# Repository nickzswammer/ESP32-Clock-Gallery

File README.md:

# ESP32 E-Paper Clock / Gallery Display

  |  | 
  |:--:| 
  | *Clock Frontside* |

A customizable ESP32-based image clock gallery project, combining Arduino firmware, Python scripting, electronics, and PCB design. This project allows users to upload images via a web interface, convert them to a binary format suitable for display on a clock-style device, and manage them on the ESP32.

---

## Features

  |  | 
  |:--:| 
  | *Power Management Block Diagram* |

- **Embedded / Microcontroller:**
  - ESP32 main controller
  - Real-Time Clock (RTC) module for accurate timekeeping
  - Pushbutton controls for menu and navigation
  - SPI and I²C interfaces for peripheral communication

- **Python Backend:**
  - Flask web server for uploading images
  - Automated image conversion to `.bin` format with dithering
  - Image resizing and centering for consistent display
  - Batch download as ZIP archives for easy transfer to the ESP32

- **Electronics & PCB:**
  - 2-layer custom PCB design
  - Integrated power circuitry with MOSFET-based power muxing
  - Battery protection and charging circuitry
  - SPI and I²C routed to peripherals for modularity

  |  | 
  |:--:| 
  | *Internal Component View* |

---

## Image Processing Workflow

1. Users upload images via the Flask web interface.
2. Images are resized to fit a **400×300 display resolution**, converted to grayscale, and dithered to 1-bit black and white.
3. The processed images are converted into a `.bin` file containing:
   - 2-byte width
   - 2-byte height
   - Pixel data in row-major order
4. All processed `.bin` files can be downloaded in a ZIP archive for easy transfer to the ESP32.

---

## Folder Structure

```

project_root/
├── image_processor/      # Python backend
│   ├── uploaded_files/       # Raw uploaded images
│   ├── processed_files/      # Converted .bin images
│   ├── zipped_files/         # Zip archives of processed images
│   ├── templates/            # Flask HTML templates
│   ├── index.html
│   ├── static/               # Optional CSS/JS for Flask
│   ├── app.py                # Flask backend and image processing
│   └── download_zip.html
├── GxEPD2_display_selection_new_style.h # GxEPD2 Library E-Paper Display Select
├── GxEPD2_selection_check.h             
├── WebHelpers.cpp                       # Helper functions for the upload/ webserver processing
├── WebHelpers.h         
├── full_disp_AND_upload.ino             # Full Arduino file containing firmware for clock functionality
└── README.md 

````
---

## ESP32 Hardware and Firmware

### Hardware

* **ESP32 Microcontroller**: Handles display updates, button input, RTC communication, and Wi-Fi connectivity.
* **GxEPD2 E-Ink Display**: SPI-connected, supports partial/full updates for low power.
* **MicroSD Card**: Stores images for display; accessed via SPI.
* **DS3231 RTC**: Provides accurate time over I²C.
* **MAX17043 Fuel Gauge**: Monitors LiPo battery percentage.
* **Buttons**: Four GPIO-connected buttons for menu navigation and mode switching.
* **Power Management**: Supports light/deep sleep; wake on button or timer.

### Firmware

* **Initialization**: Sets up peripherals, Wi-Fi, and web server.
* **Main Loop**: Handles button input, updates clock display, manages sleep, and serves web requests.
* **Gallery Management**: Reads images from SD card, navigates files, and supports slideshow.
* **Power Optimization**: Disables unused peripherals and enters sleep during inactivity.

---

## PCB & Electronics

|  | 
|:--:| 
| *PCB Layout View* |

- **2-layer PCB:**
  - Integrated power supply with custom MOSFET power muxing
  - Battery protection and charging
  - SPI and I²C routing for peripheral modules
  - ESP32 microcontroller footprint with all required signals exposed

- **Peripherals:**
  - RTC module
  - Pushbuttons for user input
  - Optional displays (LCD, OLED, or e-paper)

- **Circuit Features:**
  - Power management: allows USB and battery operation
  - Safe charging and overcurrent protection
  - Modular design for easy hardware expansion

---

## Case & Mechanical Design

- Custom enclosure design in Fusion 360 to fit the ESP32 PCB and display
- Mounting points for pushbuttons
- Openings for charging port, buttons, and display window
- 3d printed

---

## Author

**Nicholas Zhang**

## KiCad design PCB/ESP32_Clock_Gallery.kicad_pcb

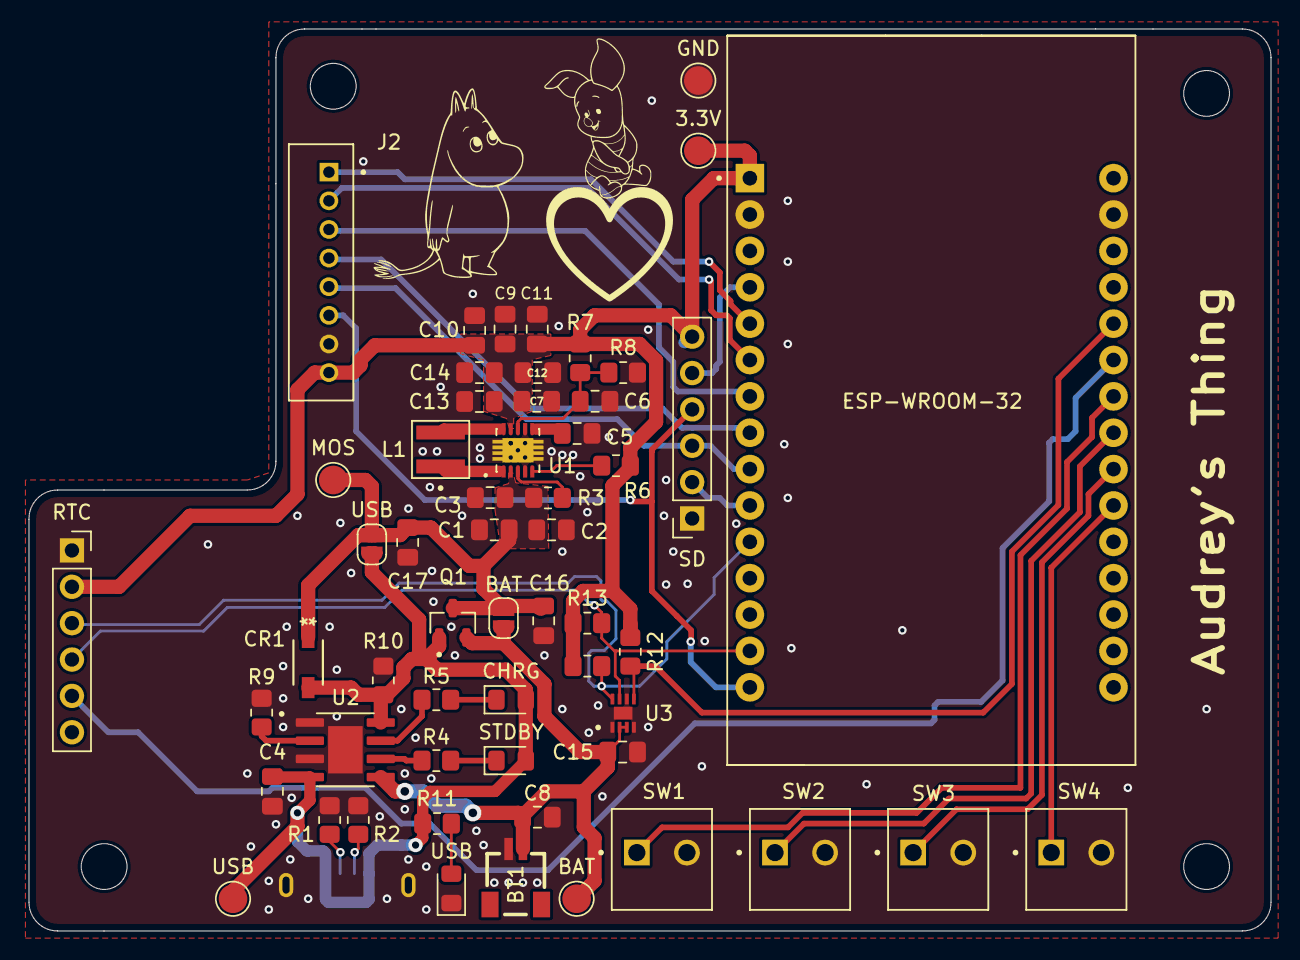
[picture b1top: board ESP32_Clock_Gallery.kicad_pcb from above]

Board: 2 copper layers, 86.8 x 63.0 mm, 57 parts (1 on the bottom side), 35 nets.

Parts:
3.3V: TestPoint; TestPoint_Pad_D2.0mm
BAT: SolderJumper_2_Open; SolderJumper-2_P1.3mm_Open_RoundedPad1.0x1.5mm
BAT#2: TestPoint; TestPoint_Pad_D2.0mm
BT1: 3.7V 1500mAh LiPo; SM02B-SRSS-TB_LF__SN_
C1, C2, C4, C8, C9, C10, C11, C12, C13, C14, C16, C17: 10uF; C_0805_2012Metric_Pad1.18x1.45mm_HandSolder
C3, C5, C7, C15: 0.1uF; C_0805_2012Metric_Pad1.18x1.45mm_HandSolder
C6: 2.2pF; C_0805_2012Metric_Pad1.18x1.45mm_HandSolder
CHRG: LED; LED_0805_2012Metric_Pad1.15x1.40mm_HandSolder
CR1: B5819W-TP; SDO_SOD-123_MCC-M
ESP-WROOM-32: ESP-WROOM-32 Dev Module; MODULE_ESP32_DEVKIT_V1
GND: TestPoint; TestPoint_Pad_D2.0mm
J1: UJC-V-G-SMT-P6-TR; SAMESKY_UJC-V-G-SMT-P6-TR
J2: B8B-PH-K-S_LF__SN_; JST_B8B-PH-K-S_LF__SN_
L1: 1.2 uH; IND_XFL4020-102MEC
MOS: TestPoint; TestPoint_Pad_D2.0mm
Q1: PMOS; SOT95P237X112-3N
R1, R2: 5.1K; R_0805_2012Metric_Pad1.20x1.40mm_HandSolder
R3, R6: 100K; R_0805_2012Metric_Pad1.20x1.40mm_HandSolder
R4, R5: 1K; R_0805_2012Metric_Pad1.20x1.40mm_HandSolder
R7: 360K; R_0805_2012Metric_Pad1.20x1.40mm_HandSolder
R8: 64.9K; R_0805_2012Metric_Pad1.20x1.40mm_HandSolder
R9: 1.5K; R_0805_2012Metric_Pad1.20x1.40mm_HandSolder
R10, R12: 10K; R_0805_2012Metric_Pad1.20x1.40mm_HandSolder
R11: 470; R_0805_2012Metric_Pad1.20x1.40mm_HandSolder
R13, R14: 4.7K; R_0805_2012Metric_Pad1.20x1.40mm_HandSolder
RTC: DS3231 Breakout; PinSocket_1x06_P2.54mm_Vertical
SD: MicroSD Breakout; PinSocket_1x06_P2.54mm_Vertical
STDBY: LED; LED_0805_2012Metric_Pad1.15x1.40mm_HandSolder
SW1, SW2, SW3, SW4: DB301V-3.5-2P-GN-S; PHOENIX_1984617
U1: TPS63060; CONV_TPS63060DSCT
U2: TP4056; SOP127P600X175-9N
U3: MAX17048G_T10; SON50P200X200X80-9N
USB: SolderJumper_2_Open; SolderJumper-2_P1.3mm_Open_RoundedPad1.0x1.5mm
USB#2: TestPoint; TestPoint_Pad_D2.0mm
USB#3: LED; LED_0805_2012Metric_Pad1.15x1.40mm_HandSolder

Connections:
+3V3: 3.3V.1, C7.1, C9.1, C10.1, C11.1, C12.1, C13.1, C14.1, ESP-WROOM-32.1 (3V3), J2.8, R6.1, R7.1, R12.1, R13.1, R14.1, RTC.2 (VCC), SD.6 (3V3), U1.9 (VOUT)
/ESP32/ALRT: ESP-WROOM-32.26 (D14), R12.2, U3.5 (~ALERT)
/ESP32/B1: ESP-WROOM-32.24 (D26), SW1.1
/ESP32/B2: ESP-WROOM-32.23 (D25), SW2.1
/ESP32/B3: ESP-WROOM-32.22 (D33), SW3.1
/ESP32/B4: ESP-WROOM-32.21 (D32), SW4.1
/ESP32/BUSY: ESP-WROOM-32.5 (D4), J2.1
/ESP32/CLK: ESP-WROOM-32.9 (D18), J2.5, SD.3 (CLK)
/ESP32/CS_DISP: ESP-WROOM-32.8 (D5), J2.4
/ESP32/CS_SD: ESP-WROOM-32.4 (D2), SD.5 (CS)
/ESP32/DC: ESP-WROOM-32.7 (TX2(17)), J2.3
/ESP32/MISO: ESP-WROOM-32.10 (D19), SD.2 (MISO)
/ESP32/MOSI: ESP-WROOM-32.15 (D23), J2.6, SD.4 (MOSI)
/ESP32/RST: ESP-WROOM-32.6 (RX2(16)), J2.2
/ESP32/SCL: ESP-WROOM-32.14 (D22), R13.2, RTC.4 (SCL), U3.7 (SCL)
/ESP32/SDA: ESP-WROOM-32.11 (D21), R14.2, RTC.3 (SDA), U3.8 (SDA)
/ESP32/SQW: ESP-WROOM-32.25 (D27), RTC.5 (SQW)
/Power/3.7V_BAT: BAT.1 (A), BAT#2.1, BT1.2 (-), C8.1, C15.1, Q1.2, U2.5 (BAT), U3.2 (CELL), U3.3 (VDD)
/Power/5V_USB: C4.1, CHRG.2 (A), CR1.2, J1.A9 (VBUS), J1.B9 (VBUS__1), Q1.1, R10.1, R11.2, STDBY.2 (A), U2.4 (VCC), U2.8 (CE), USB.1 (A), USB#2.1
/Power/MOS_OUT: BAT.2 (B), C1.1, C2.1, C3.1, C16.1, C17.1, CR1.1, MOS.1, Q1.3, R3.1, U1.2 (VIN), USB.2 (B)
GND: BT1.1 (+), C1.2, C2.2, C3.2, C4.2, C5.2, C6.2, C7.2, C8.2, C9.2, C10.2, C11.2, C12.2, C13.2, C14.2, C15.2, C16.2, C17.2, ESP-WROOM-32.2 (GND), ESP-WROOM-32.29 (GND), GND.1, J1.A12 (GND), J1.B12 (GND__1), J1.SH1 (SHIELD), J1.SH2 (SHIELD__1), J2.7, R1.1, R2.1, R8.2, R9.1, R10.2, RTC.1 (GND), SD.1 (GND), SW1.2, SW2.2, SW3.2, SW4.2, U1.4 (PS/SYNC), U1.7 (GND), U1.11 (PGND), U1.12, U1.13, U1.14, U1.15, U1.16, U2.1 (TEMP), U2.3 (GND), U2.9 (EP), U3.1 (CTG), U3.4 (GND), U3.6 (QSTRT), U3.9 (EP), USB#3.1 (K)
unnamed: R4.2, STDBY.1 (K)
unnamed: CHRG.1 (K), R5.2
unnamed: R11.1, USB#3.2 (A)
unnamed: J1.A5 (CC1), R2.2
unnamed: J1.B5 (CC2), R1.2
unnamed: R3.2, U1.3 (EN)
unnamed: C6.1, R7.2, R8.1, U1.8 (FB)
unnamed: L1.1, U1.1 (L1)
unnamed: L1.2, U1.10 (L2)
unnamed: R6.2, U1.5 (PG)
unnamed: C5.1, U1.6 (VAUX)
unnamed: R9.2, U2.2 (PROG)
unnamed: R5.1, U2.7 (~CHRG)
unnamed: R4.1, U2.6 (~STDBY)

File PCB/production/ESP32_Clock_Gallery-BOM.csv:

"Reference","Value","Datasheet","Footprint","Qty","DNP"
"BT1","3.7V 1500mAh LiPo","~","SM02B-SRSS-TB_LF__SN_:SM02B-SRSS-TB_LF__SN_","1",""
"C1,C2,C4,C8,C9,C10,C11,C12,C13,C14,C16,C17","10uF","~","Capacitor_SMD:C_0805_2012Metric_Pad1.18x1.45mm_HandSolder","12",""
"C3,C5,C7,C15","0.1uF","~","Capacitor_SMD:C_0805_2012Metric_Pad1.18x1.45mm_HandSolder","4",""
"C6","2.2pF","~","Capacitor_SMD:C_0805_2012Metric_Pad1.18x1.45mm_HandSolder","1",""
"CR1","B5819W-TP","B5819W-TP","B5819SW:SDO_SOD-123_MCC-M","1",""
"D1,D2,D3","LED","~","LED_SMD:LED_0805_2012Metric_Pad1.15x1.40mm_HandSolder","3",""
"J1","UJC-V-G-SMT-P6-TR","","UJC_V_G_SMT_P6_TR:SAMESKY_UJC-V-G-SMT-P6-TR","1",""
"J2","B8B-PH-K-S_LF__SN_","","B8B-PH-K-S_LF__SN_:JST_B8B-PH-K-S_LF__SN_","1",""
"L1","1.2 uH","~","XFL4020-102MEC:IND_XFL4020-102MEC","1",""
"Q1","PMOS","","IRLML6402TRPBF:SOT95P237X112-3N","1",""
"R1,R2","5.1K","~","Resistor_SMD:R_0805_2012Metric_Pad1.20x1.40mm_HandSolder","2",""
"R3,R6","100K","~","Resistor_SMD:R_0805_2012Metric_Pad1.20x1.40mm_HandSolder","2",""
"R4,R5","1K","~","Resistor_SMD:R_0805_2012Metric_Pad1.20x1.40mm_HandSolder","2",""
"R7","360K","~","Resistor_SMD:R_0805_2012Metric_Pad1.20x1.40mm_HandSolder","1",""
"R8","64.9K","~","Resistor_SMD:R_0805_2012Metric_Pad1.20x1.40mm_HandSolder","1",""
"R9","1.5K","~","Resistor_SMD:R_0805_2012Metric_Pad1.20x1.40mm_HandSolder","1",""
"R10,R12","10K","~","Resistor_SMD:R_0805_2012Metric_Pad1.20x1.40mm_HandSolder","2",""
"R11","470","~","Resistor_SMD:R_0805_2012Metric_Pad1.20x1.40mm_HandSolder","1",""
"R13,R14","4.7K","~","Resistor_SMD:R_0805_2012Metric_Pad1.20x1.40mm_HandSolder","2",""
"SW1,SW2,SW3,SW4","DB301V-3.5-2P-GN-S","~","1984617:PHOENIX_1984617","4",""
"TP1,TP2,TP3,TP4,TP5","TestPoint","~","TestPoint:TestPoint_Pad_D2.0mm","5",""
"U1","TPS63060","http://www.ti.com/lit/ds/symlink/tps63060.pdf","TPS63060DSCT:CONV_TPS63060DSCT","1",""
"U2","TP4056","","TP4056:SOP127P600X175-9N","1",""
"U3","MAX17048G_T10","","MAX17048G_T10:SON50P200X200X80-9N","1",""
"U4","DS3231 Breakout","","Connector_PinSocket_2.54mm:PinSocket_1x06_P2.54mm_Vertical","1",""
"U5","MicroSD Breakout","","Connector_PinSocket_2.54mm:PinSocket_1x06_P2.54mm_Vertical","1",""
"U6","ESP-WROOM-32 Dev Module","","ESP32-DEVKIT-V1:MODULE_ESP32_DEVKIT_V1","1",""

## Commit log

2025-04-23 Combined batch_convert and bin function
2025-04-23 Remove Files
2025-04-23 I2S Square Wave Testing
2025-04-23 Real Adding Now
2025-05-13 Pre Image Processor
2025-05-13 Add SD Wireless Upload
2025-05-14 Flask Server Processing Complete
2025-05-14 Remove VEnv
2025-05-14 Update Gitignore
2025-05-14 Update App Name FLASK
2025-05-14 Img -> Dithered Bin Complete
2025-05-14 Update Git Ignore
2025-05-15 Combined
2025-05-15 Remove DNS
2025-05-15 What
2025-05-16 Enabled Scroll (STILL HAVE TO BEAUTIFY)
2025-05-17 Completed Display and Scroll For Real
2025-05-17 Combined Working Display + Upload
2025-05-18 Modularized Web Helpers, also added 4th button reverse
2025-05-18 Rearranged Buttons + Made some Beautification
2025-05-18 Added Secrets
2025-05-19 Pagination Test
2025-05-27 Styled + Pagination Completed
2025-05-28 RTC Enabled
2025-05-29 Added Clock Display (Battery, Date, Time, Annotations) and Hold Button Functionality - STill need to fix battery percentage bar
2025-06-03 Folder Structure
2025-06-03 Add PCB
2025-06-08 PCB Routing
2025-06-17 Hello
2025-06-20 Full Functionality + Sleep
2025-06-22 ALRT Functionality
2025-07-18 Schematic PDF
2025-08-18 Most Recent?
2025-08-19 Recent Patch
2025-11-23 Remove extra line breaks in README.md
2025-11-23 Update README with images and project details
    Added images and enhanced project description in README.
2025-11-23 Add PCB layout image to README
2025-11-23 Added Images
